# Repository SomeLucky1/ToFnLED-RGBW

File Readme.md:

# ToFnLED-RGBW
ToF sensor + RGBW LED

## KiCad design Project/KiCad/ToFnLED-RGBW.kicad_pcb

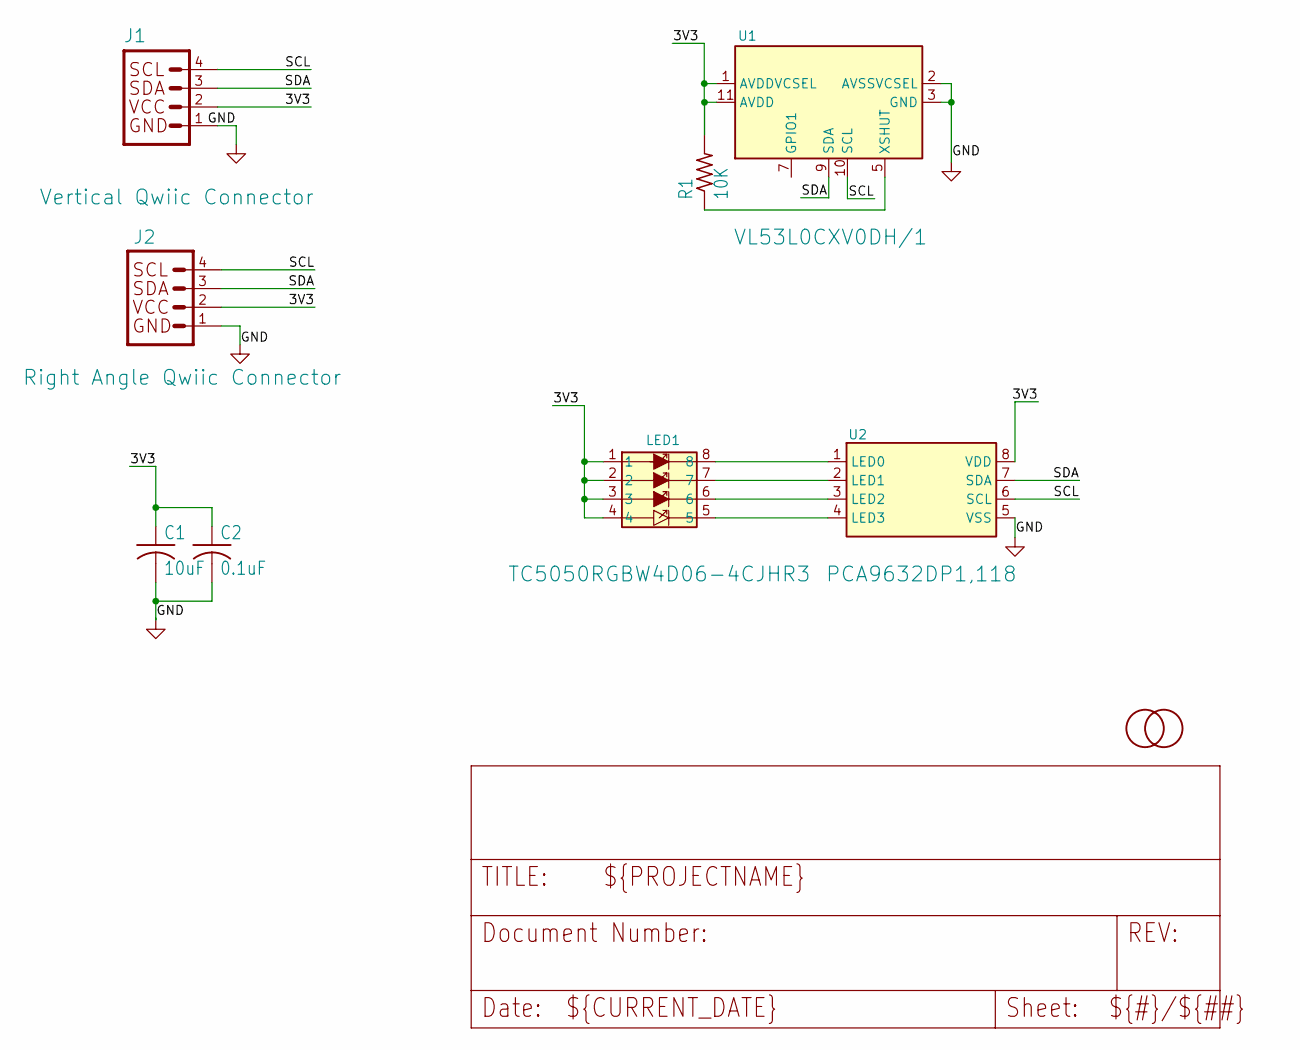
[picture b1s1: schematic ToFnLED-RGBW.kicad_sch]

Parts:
C1: 10uF; C_0603_1608Metric; LCSC C19702
C2: 0.1uF; C_0603_1608Metric; LCSC C1591
J1: Vertical Qwiic Connector; JST04_1MM_VERT; LCSC C160390
J2: Right Angle Qwiic Connector; JST_SH_SM04B-SRSS-TB_1x04-1MP_P1.00mm_Horizontal
LED1: TC5050RGBW4D06-4CJHR3; LED_RGBW_5050-8
R1: 10K; R_0603_1608Metric; LCSC C98220
U1: VL53L0CXV0DH/1; ST_VL53L0X
U2: PCA9632DP1,118; TSSOP-8_3x3mm_P0.65mm
U$1, U$2: FIDUCIAL; Fiducial_1mm_Mask2mm

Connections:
/3V3: C1.1, C2.1, J1.2, J2.2, LED1.1, LED1.2, LED1.3, LED1.4, R1.2, U1.1 (AVDDVCSEL), U1.11 (AVDD), U2.8 (VDD)
/SCL: J1.4, J2.4, U1.10 (SCL), U2.6 (SCL)
/SDA: J1.3, J2.3, U1.9 (SDA), U2.7 (SDA)
GND: C1.2, C2.2, J1.1, J1.NC1 (Housing), J1.NC2 (Housing), J2.1, J2.MP (Housing), U1.2 (AVSSVCSEL), U1.3 (GND), U1.4 (GND), U1.6 (GND), U1.12 (GND), U2.5 (VSS)
unnamed: R1.1, U1.5 (XSHUT)
unnamed: LED1.8, U2.1 (LED0)
unnamed: LED1.7, U2.2 (LED1)
unnamed: LED1.6, U2.3 (LED2)
unnamed: LED1.5, U2.4 (LED3)

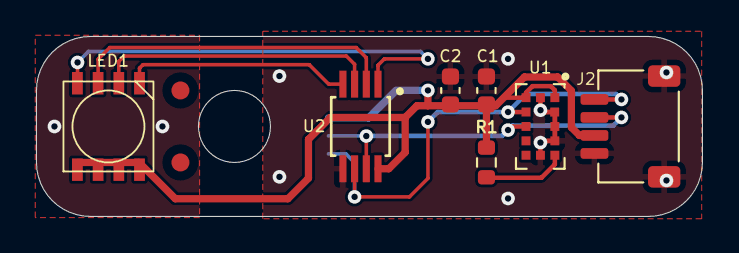
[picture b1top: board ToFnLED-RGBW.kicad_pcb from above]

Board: 2 copper layers, 37.0 x 10.0 mm, 10 parts (1 on the bottom side), 9 nets.

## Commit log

2023-07-28 Adding KiCad files
2023-07-28 All project symbols
2023-07-28 3D Parts
2023-07-29 Added full KiCad project
2023-07-29 KiCad generated Gerbers/Drill
2023-07-29 Updated BOM and CPL files.
2023-08-02 ToF model rotation fix.
2023-08-10 KiCad project and export updates
2023-08-12 Silk screen updates
2023-08-12 solder pad updates
2023-08-17 Updated designs
